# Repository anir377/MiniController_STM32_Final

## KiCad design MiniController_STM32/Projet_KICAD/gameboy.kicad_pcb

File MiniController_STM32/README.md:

# Mini-console STM32 — Projet PCB

Projet réalisé en binôme dans le cadre de la 5e année à **Polytech Nice Sophia**, en spécialité systèmes embarqués.

## Présentation du projet

Notre objectif est de concevoir une carte électronique pour une mini-console de jeu portable. Elle doit réunir un écran TFT, des commandes de jeu, un lecteur microSD, une sortie audio et un moteur vibrant pour le retour haptique. Le travail porte actuellement sur la conception du schéma électronique sous KiCad, le choix des composants et la préparation du futur PCB.

Le microcontrôleur retenu est le **STM32F405RGT6** (ARM Cortex-M4, 168 MHz, 1 Mo de Flash et 192 Ko de RAM), monté directement sur notre carte.

## Composants et blocs électroniques

L'alimentation est prévue à partir d'un **connecteur USB-C**, avec des composants de protection et un convertisseur abaisseur **TLV62569DBV** pour obtenir les 3,3 V nécessaires au système. Les condensateurs de découplage du STM32 ont également été ajoutés. Une alimentation sur batterie est envisagée, mais son circuit de charge et de gestion reste à concevoir.

Pour l'affichage, nous avons prévu un **écran TFT SPI de 4 pouces (480 × 320 pixels)**. Une interface **microSD**, accessible sur le module écran, utilise une liaison SPI distincte pour le stockage des ressources ou des jeux. Les commandes comprennent un **joystick analogique à deux axes avec bouton intégré** et des boutons supplémentaires, notamment Start et Select.

La partie audio comporte un circuit d'amplification et un connecteur pour haut-parleur ; elle est encore en cours de finalisation. Nous avons aussi ajouté un **moteur vibrant ERM** (LCM1027A2445F), commandé par un MOSFET AO3400A et un signal PWM du STM32, avec diode de protection et composants associés.

Le schéma prévoit par ailleurs un **quartz externe (HSE)**, un connecteur de programmation/débogage de type **JTAG/SWD** et un connecteur UART pour le diagnostic. Ces interfaces doivent encore être vérifiées et raccordées complètement.

## Configuration du STM32

Nous utilisons **STM32CubeMX** pour préparer l'affectation des broches et des périphériques du STM32. Le fichier `MiniConsole_STM32.ioc` contient notamment les configurations de SPI1 pour l'écran, SPI2 pour la microSD, ADC1 pour le joystick et TIM4 pour la commande PWM du moteur vibrant.

Ces choix doivent rester cohérents avec les connexions du schéma KiCad. Le développement et les essais du firmware ne constituent pas encore un livrable terminé.

## Avancement et travail restant

Les principaux blocs de la mini-console sont maintenant représentés dans le schéma. **Le projet est encore en phase de conception et n'est pas prêt à être fabriqué.** Il reste notamment à vérifier l'ensemble des réseaux d'alimentation, terminer les connexions de programmation, du quartz, des boutons et de l'audio, ainsi qu'à valider les caractéristiques et les empreintes des composants.

Les prochaines étapes seront la correction des erreurs ERC, la finalisation des bibliothèques et des références JLCPCB, puis le placement et le routage du **PCB quatre couches**, avant la préparation des fichiers de fabrication et d'assemblage.

## Fichiers du dépôt

- **[Projet KiCad](Projet_KICAD/Projet_PCBPolytech_git.kicad_pro)** : projet électronique à ouvrir dans KiCad.
- **[Schéma KiCad](Projet_KICAD/Projet_PCBPolytech_git.kicad_sch)** : schéma électrique en cours de réalisation.
- **[Configuration STM32CubeMX](MiniConsole_STM32.ioc)** : affectation des broches et configuration des périphériques.

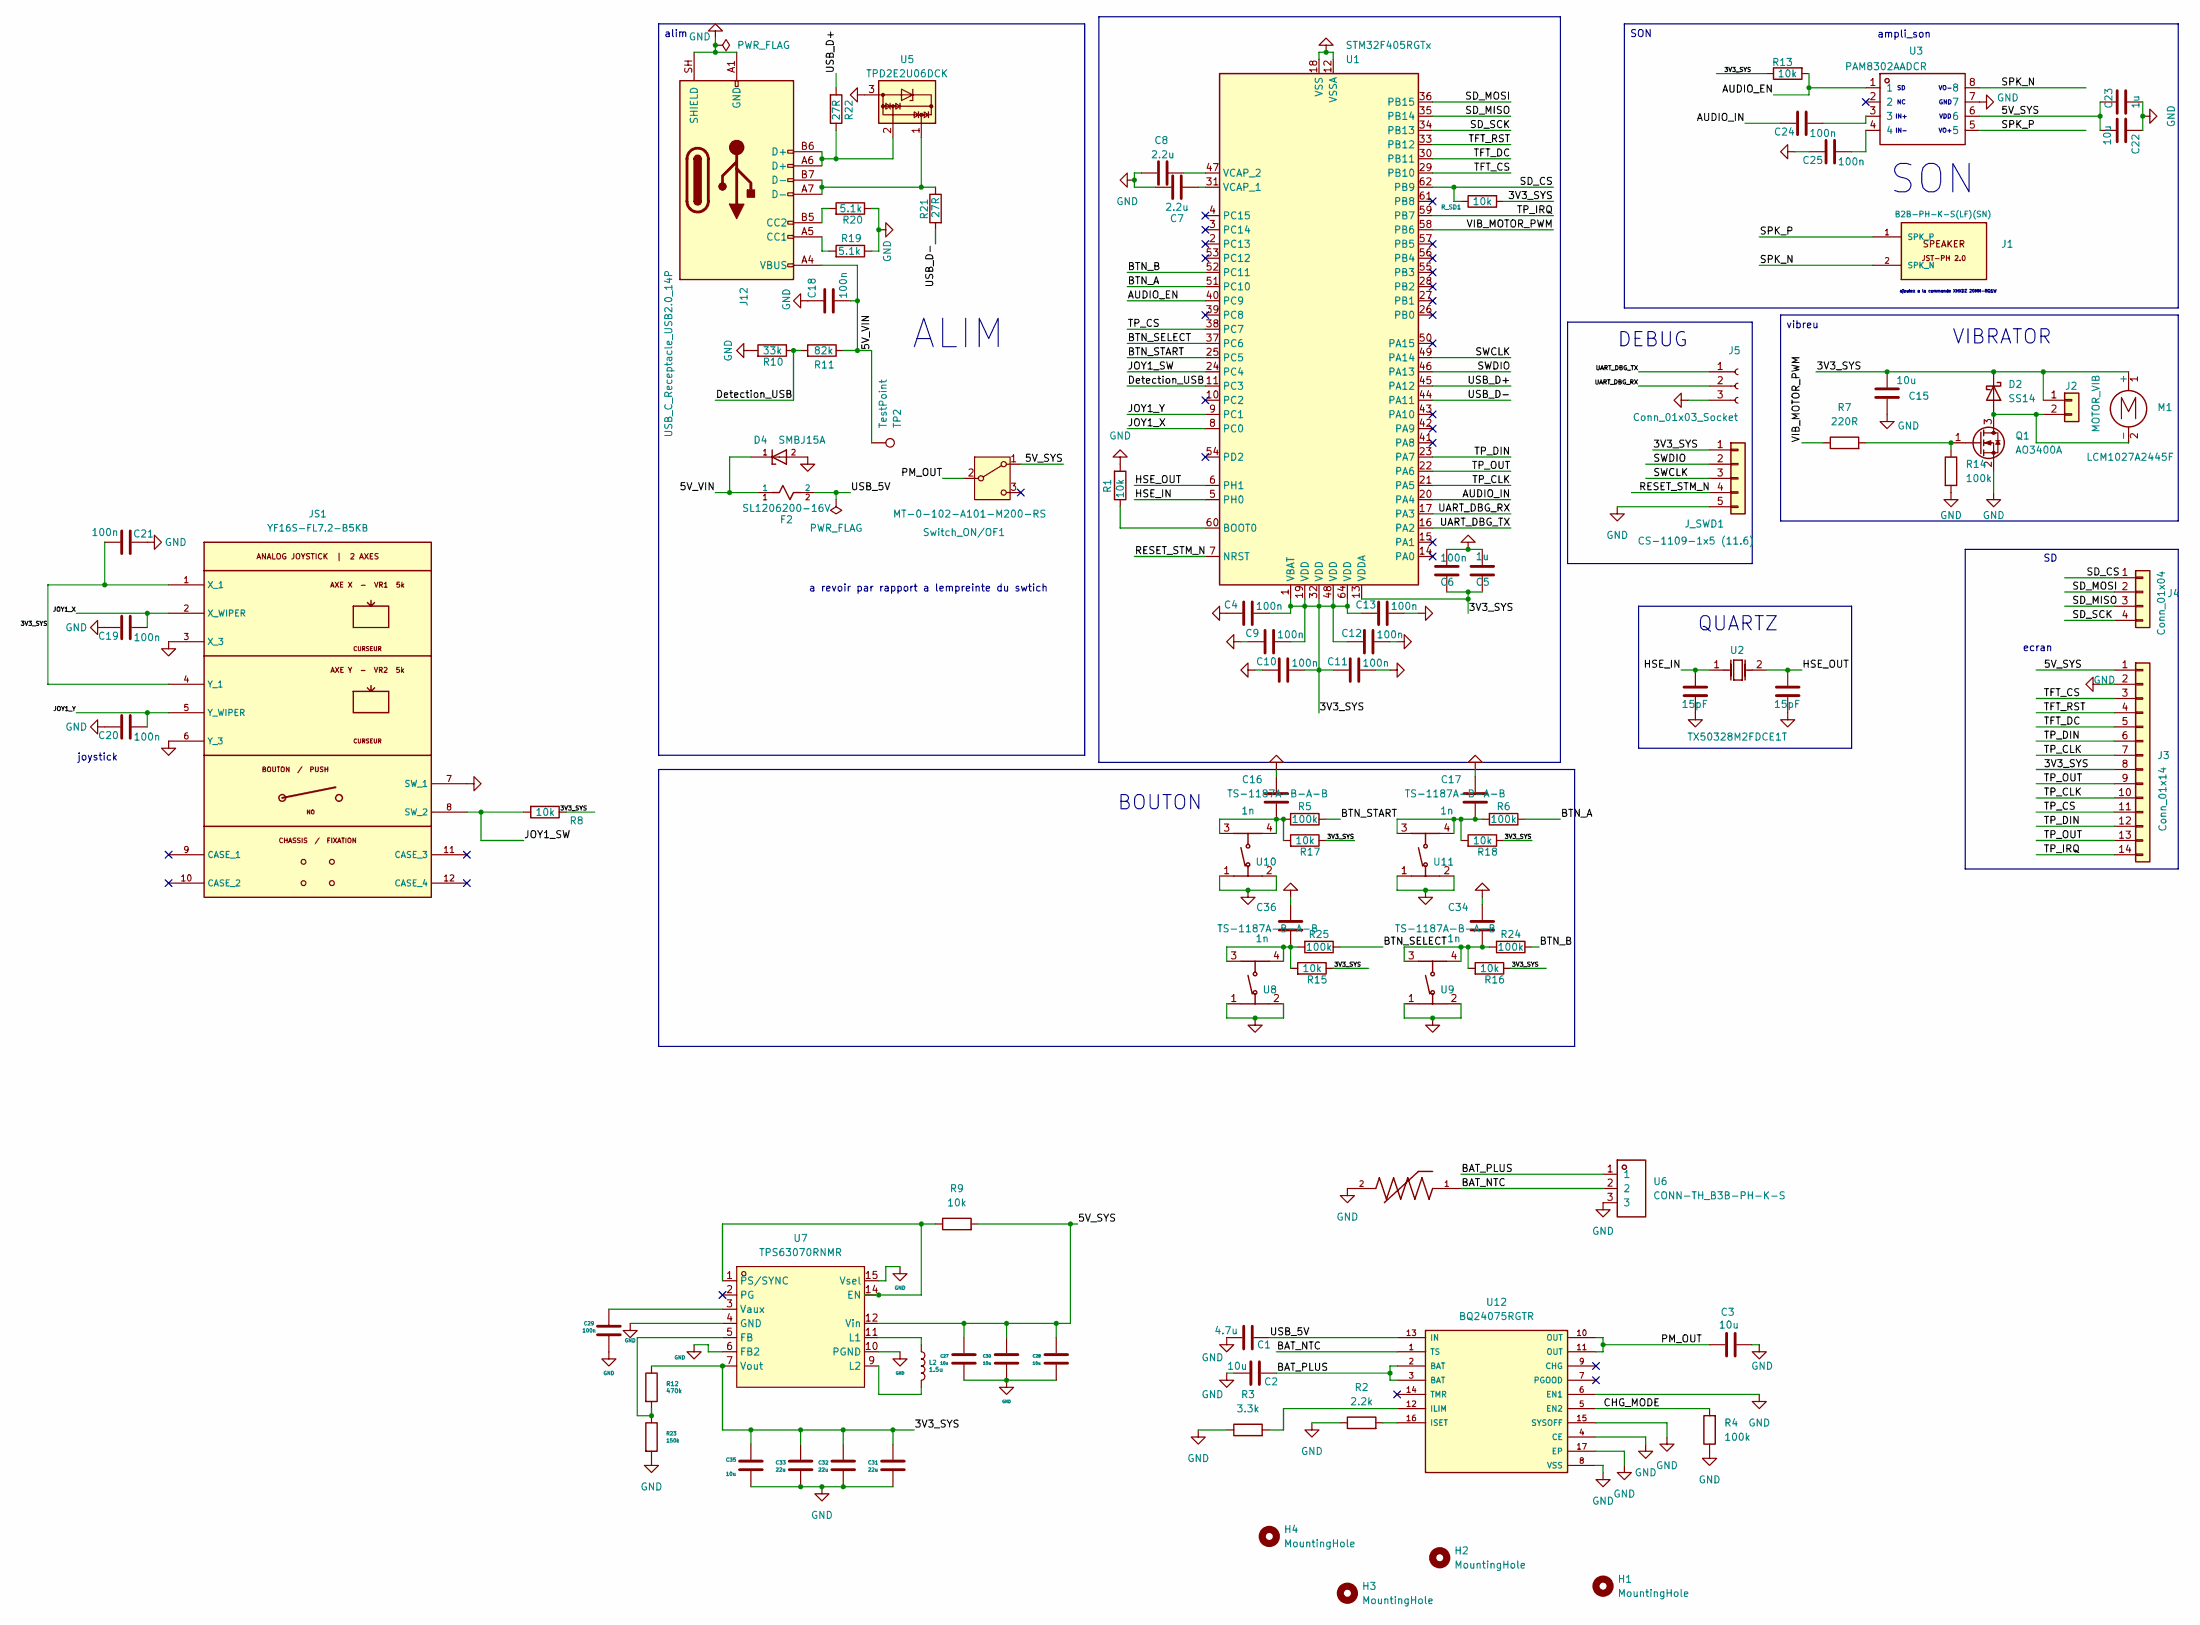
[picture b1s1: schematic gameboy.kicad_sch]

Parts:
C1: 4.7u; C_0805_2012Metric; LCSC C49326719
C2, C3, C15, C22, C27, C28, C30: 10u; C_0805_2012Metric; LCSC C15850
C4, C6, C9, C10, C11, C12, C18, C19, C20, C21, C24, C25, C29: 100n; C_0603_1608Metric; LCSC C14663
C5: 1u; C_0805_2012Metric
C7, C8: 2.2u; C_0805_2012Metric; LCSC C1731
C13: 100n; C_0805_2012Metric; LCSC C14663
C14, C26: 15pF; C_0603_1608Metric
C16, C17, C34, C36: 1n; C_0603_1608Metric; LCSC C131031
C23: 1u; C_0805_2012Metric; LCSC C376925
C31, C32, C33: 22u; C_1206_3216Metric; LCSC C12891
C35: 10u; C_0805_2012Metric
D2: SS14; D_SMA; LCSC C2480
D4: SMBJ15A; D_SMB; PARTREV F2102; LCSC C357961
F2: SL1206200-16V; Fuse_1206_3216Metric; LCSC C50766782
H1, H2, H3, H4: MountingHole; MountingHole_2.2mm_M2
J1: B2B-PH-K-S(LF)(SN); JST_PH_B2B-PH-K_1x02_P2.00mm_Vertical; LCSC Part C131337
J2: MOTOR_VIB; SolderWire-0.1sqmm_1x02_P3.6mm_D0.4mm_OD1mm_Relief
J3: Conn_01x14; PinSocket_1x14_P2.54mm_Vertical; LCSC C2905420
J4: Conn_01x04; PinSocket_1x04_P2.54mm_Vertical; LCSC C2897367
J5: Conn_01x03_Socket; PinHeader_1x03_P2.54mm_Vertical; LCSC C49257
J12: USB_C_Receptacle_USB2.0_14P; USB_C_Receptacle_GCT_USB4085; LCSC C7095263
JS1: YF16S-FL7.2-B5KB; JOYTICK-TH_YF16S-FL7_2-B5KB-45-10-Y_1_YF16S-FL7_2-B5KB_45-1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; MPN YF16S-FL7.2-B5Kb(45-10)-Y; LCSC Part C37323740
J_SWD1: CS-1109-1x5 (11.6); PinHeader_1x05_P2.54mm_Vertical; LCSC C5156614
L2: 1.5u; L_Coilcraft_XxL4020; LCSC Part # C3033018
M1: LCM1027A2445F; LCSC C2759984
Q1: AO3400A; SOT-23; LCSC C20917
R1: 10k; R_0603_1608Metric; LCSC C25804
R2: 2.2k; R_0603_1608Metric; LCSC C4190
R3: 3.3k; R_0603_1608Metric
R4, R5, R6, R14, R24, R25: 100k; R_0603_1608Metric; LCSC C25803
R7: 220R; R_0603_1608Metric; LCSC C22962
R8, R9, R13, R15, R16, R17, R18: 10k; R_0805_2012Metric; LCSC C17414
R10: 33k; R_0603_1608Metric; LCSC C4216
R11: 82k; R_0603_1608Metric; LCSC C23254
R12: 470k; R_0603_1608Metric; LCSC C23178
R19, R20: 5.1k; R_0805_2012Metric; LCSC C2912598
R21, R22: 27R; R_0805_2012Metric; LCSC C2889467
R23: 150k; R_0603_1608Metric; LCSC C22807
RT1: NCP18XH103F03RB; R_0603_1608Metric; LCSC C13564
R_SD1: 10k; R_0603_1608Metric; LCSC C25804
Switch_ON/OF1: MT-0-102-A101-M200-RS; SW-SMD_4P-L5.1-W5.1-P3.70-LS6.5-TL_H1.5; LCSC C1788492
TP2: TestPoint; TestPoint_Pad_D2.0mm
U1: STM32F405RGTx; LQFP-64_10x10mm_P0.5mm; LCSC Part # C15742
U2: TX50328M2FDCE1T; Crystal_SMD_5032-2Pin_5.0x3.2mm; LCSC C5182763
U3: PAM8302AADCR; MSOP-8_3x3mm_P0.65mm; LCSC C113367
U5: TPD2E2U06DCK; SOT-323_SC-70; LCSC C915089
U6: CONN-TH_B3B-PH-K-S; JST_PH_B3B-PH-K_1x03_P2.00mm_Vertical; LCSC C131339
U7: TPS63070RNMR; VQFN-15_L3.0-W2.5-P0.50-BL; MPN TPS63070RNMR; LCSC Part C109322
U8, U9, U10, U11: TS-1187A-B-A-B; SW-SMD_4P-L5.1-W5.1-P3.70-LS6.5-TL_H1.5; LCSC C318884
U12: BQ24075RGTR; VQFN-16-1EP_3x3mm_P0.5mm_EP1.68x1.68mm; LCSC Part # C15464

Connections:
/3V3_SYS: C4.2, C5.1, C6.1, C9.2, C10.2, C11.1, C12.1, C13.1, C15.2, C21.1, C31.1, C32.1, C33.1, C35.1, D2.1 (K), J2.1, J3.8, JS1.1 (X_1), JS1.4 (Y_1), J_SWD1.1, M1.1 (+), R8.1, R12.1, R13.1, R15.1, R16.1, R17.1, R18.1, R_SD1.2, U1.1 (VBAT), U1.13 (VDDA), U1.19 (VDD), U1.32 (VDD), U1.48 (VDD), U1.64 (VDD), U7.7 (Vout)
/5V_SYS: C22.2, C23.1, C27.1, C28.1, C30.1, J3.1, R9.2, Switch_ON/OF1.1 (A), U3.6, U7.12 (Vin)
/5V_VIN: C18.2, D4.1, F2.1, J12.A4 (VBUS), J12.A9 (VBUS), J12.B4 (VBUS), J12.B9 (VBUS), R11.1, TP2.1 (1_1)
/AUDIO_EN: R13.2, U1.40 (PC9), U3.1
/AUDIO_IN: C24.2, U1.20 (PA4)
/BAT_NTC: RT1.1, U6.2, U12.1 (TS)
/BAT_PLUS: C2.1, U6.1, U12.2 (BAT), U12.3 (BAT)
/BTN_A: R6.1, U1.51 (PC10)
/BTN_B: R24.1, U1.52 (PC11)
/BTN_SELECT: R25.1, U1.37 (PC6)
/BTN_START: R5.1, U1.25 (PC5)
/CHG_MODE: R4.2, U12.5 (EN2)
/Detection_USB: R10.1, R11.2, U1.11 (PC3)
/HSE_IN: C14.2, U1.5 (PH0), U2.1
/HSE_OUT: C26.2, U1.6 (PH1), U2.2
/JOY1_SW: JS1.8 (SW_2), R8.2, U1.24 (PC4)
/JOY1_X: C19.1, JS1.2 (X_WIPER), U1.8 (PC0)
/JOY1_Y: C20.1, JS1.5 (Y_WIPER), U1.9 (PC1)
/PM_OUT: C3.1, Switch_ON/OF1.2 (B), U12.10 (OUT), U12.11 (OUT)
/RESET_STM_N: J_SWD1.4, U1.7 (NRST)
/SD_CS: J4.1, R_SD1.1, U1.62 (PB9)
/SD_MISO: J4.3, U1.35 (PB14)
/SD_MOSI: J4.2, U1.36 (PB15)
/SD_SCK: J4.4, U1.34 (PB13)
/SPK_N: J1.2 (SPK_N), U3.8
/SPK_P: J1.1 (SPK_P), U3.5
/SWCLK: J_SWD1.3, U1.49 (PA14)
/SWDIO: J_SWD1.2, U1.46 (PA13)
/TFT_CS: J3.3, U1.29 (PB10)
/TFT_DC: J3.5, U1.30 (PB11)
/TFT_RST: J3.4, U1.33 (PB12)
/TP_CLK: J3.7, J3.10, U1.21 (PA5)
/TP_CS: J3.11, U1.38 (PC7)
/TP_DIN: J3.6, J3.12, U1.23 (PA7)
/TP_IRQ: J3.14, U1.59 (PB7)
/TP_OUT: J3.9, J3.13, U1.22 (PA6)
/UART_DBG_RX: J5.2, U1.17 (PA3)
/UART_DBG_TX: J5.1, U1.16 (PA2)
/USB_5V: C1.1, F2.2, U12.13 (IN)
/USB_D+: R22.2, U1.45 (PA12)
/USB_D-: R21.2, U1.44 (PA11)
/VIB_MOTOR_PWM: R7.1, U1.58 (PB6)
GND: C1.2, C2.2, C3.2, C4.1, C5.2, C6.2, C7.1, C8.1, C9.1, C10.1, C11.2, C12.2, C13.2, C14.1, C15.1, C16.1, C17.1, C18.1, C19.2, C20.2, C21.2, C22.1, C23.2, C25.2, C26.1, C27.2, C28.2, C29.2, C30.2, C31.2, C32.2, C33.2, C34.1, C35.2, C36.1, D4.2, J3.2, J5.3, J12.A1 (GND), J12.A12 (GND), J12.B1 (GND), J12.B12 (GND), J12.SH (SHIELD), JS1.3 (X_3), JS1.6 (Y_3), JS1.7 (SW_1), J_SWD1.5, Q1.2 (S), R1.2, R2.1, R3.1, R4.1, R10.2, R14.2, R19.1, R20.1, R23.2, RT1.2, U1.12 (VSSA), U1.18 (VSS), U1.63 (VSS), U3.7, U5.3, U6.3, U7.4 (GND), U7.6 (FB2), U7.10 (PGND), U7.15 (Vsel), U8.1, U8.2, U9.1, U9.2, U10.1, U10.2, U11.1, U11.2, U12.4 (CE), U12.6 (EN1), U12.8 (VSS), U12.15 (SYSOFF), U12.17 (EP)
unnamed: C16.2, R5.2, R17.2, U10.3, U10.4
unnamed: C17.2, R6.2, R18.2, U11.3, U11.4
unnamed: C24.1, U3.3
unnamed: C25.1, U3.4
unnamed: C34.2, R16.2, R24.2, U9.3, U9.4
unnamed: C36.2, R15.2, R25.2, U8.3, U8.4
unnamed: D2.2 (A), J2.2, M1.2 (-), Q1.3 (D)
unnamed: J12.A5 (CC1), R19.2
unnamed: J12.B5 (CC2), R20.2
unnamed: J12.A6 (D+), J12.B6 (D+), R22.1, U5.2
unnamed: J12.A7 (D-), J12.B7 (D-), R21.1, U5.1
unnamed: Q1.1 (G), R7.2, R14.1
unnamed: R1.1, U1.60 (BOOT0)
unnamed: C7.2, U1.31 (VCAP_1)
unnamed: C8.2, U1.47 (VCAP_2)
unnamed: R9.1, U7.1 (PS/SYNC), U7.14 (EN)
unnamed: R12.2, R23.1, U7.5 (FB)
unnamed: L2.1, U7.11 (L1)
unnamed: L2.2, U7.9 (L2)
unnamed: C29.1, U7.3 (Vaux)
unnamed: R3.2, U12.12 (ILIM)
unnamed: R2.2, U12.16 (ISET)

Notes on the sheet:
ampli_son
IN-
QUARTZ
ecran
VO+
VDD
VO-
SON
a revoir par rapport a lempreinte du swtich
GND
IN+
joystick
DEBUG
ALIM
BOUTON
VIBRATOR
ajoutez a la commande XHXDZ 20MM-8Ω1W
vibreu
alim

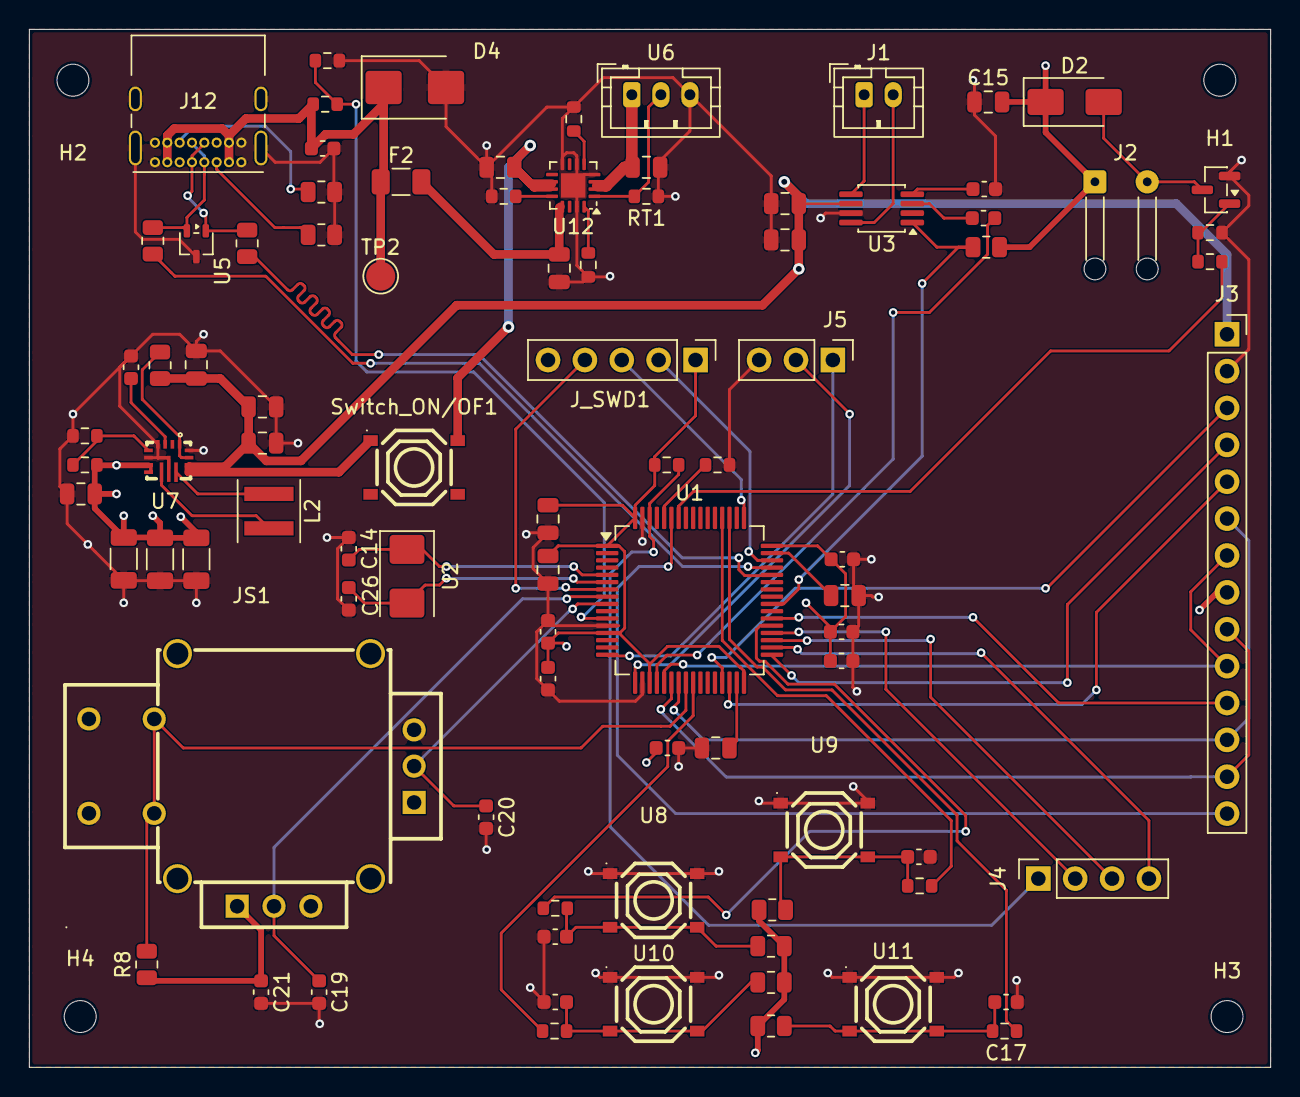
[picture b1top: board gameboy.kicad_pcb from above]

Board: 4 copper layers, 85.5 x 71.5 mm, 93 parts (0 on the bottom side), 65 nets.

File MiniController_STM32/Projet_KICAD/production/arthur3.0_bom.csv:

Designator,Footprint,Quantity,Value,LCSC Part #
C1,0805,1,4.7u,C49326719
"C10, C11, C12, C18, C19, C20, C21, C24, C25, C29, C4, C6, C9",0603,13,100n,C14663
C13,0805,1,100n,C14663
"C14, C26",0603,2,15pF,
"C15, C2, C22, C27, C28, C3, C30",0805,7,10u,C15850
"C16, C17, C34, C36",0603,4,1n,C131031
C23,0805,1,1u,C376925
"C31, C32, C33",1206,3,22u, C12891
C35,0805,1,10u,
C5,0805,1,1u,
"C7, C8",0805,2,2.2u,C1731
D2,D_SMA,1,SS14,C2480
D4,D_SMB,1,SMBJ15A,C357961
F2,1206,1,SL1206200-16V,C50766782
J1,JST_PH_B2B-PH-K_1x02_P2.00mm_Vertical,1,B2B-PH-K-S(LF)(SN),C131337
J12,USB_C_Receptacle_GCT_USB4085,1,USB_C_Receptacle_USB2.0_14P,C7095263
J2,SolderWire-0.1sqmm_1x02_P3.6mm_D0.4mm_OD1mm_Relief,1,MOTOR_VIB,
J3,PinSocket_1x14_P2.54mm_Vertical,1,Conn_01x14,C2905420
J4,PinSocket_1x04_P2.54mm_Vertical,1,Conn_01x04,C2897367
J5,PinHeader_1x03_P2.54mm_Vertical,1,Conn_01x03_Socket,C49257
JS1,JOYTICK-TH_YF16S-FL7_2-B5KB-45-10-Y_1_YF16S-FL7_2-B5KB_45-10_-Y_C37323740,1,YF16S-FL7.2-B5KB,C37323740
J_SWD1,PinHeader_1x05_P2.54mm_Vertical,1,CS-1109-1x5 (11.6),C5156614
L2,L_Coilcraft_XxL4020,1,1.5u,C3033018
Q1,SOT-23,1,AO3400A,C20917
R1,0603,1,10k,C25804
R10,0603,1,33k,C4216
R11,0603,1,82k,C23254
R12,0603,1,470k,C23178
"R13, R15, R16, R17, R18, R8, R9",0805,7,10k,C17414
R14,0603,1,100k,C25803
"R19, R20",0805,2,5.1k,C2912598
R2,0603,1,2.2k, C4190
R21,0805,1,27R,C2889467
R22,0805,1,27R,C2889467 
R23,0603,1,150k,C22807
"R24, R25, R4, R5, R6",0603,5,100k, C25803
R3,0603,1,3.3k,
R7,0603,1,220R,C22962
RT1,0603,1,NCP18XH103F03RB,C13564
R_SD1,0603,1,10k, C25804
SWITCH_ON/OF1,SW-SMD_4P-L5.1-W5.1-P3.70-LS6.5-TL_H1.5,1,MT-0-102-A101-M200-RS,C318884
TP2,TestPoint_Pad_D2.0mm,1,TestPoint,
U1,LQFP-64_10x10mm_P0.5mm,1,STM32F405RGTx,C15742
"U10, U11, U8, U9",SW-SMD_4P-L5.1-W5.1-P3.70-LS6.5-TL_H1.5,4,TS-1187A-B-A-B,C318884
U12,VQFN-16-1EP_3x3mm_P0.5mm_EP1.68x1.68mm,1,BQ24075RGTR,C15464
U2,Crystal_SMD_5032-2Pin_5.0x3.2mm,1,TX50328M2FDCE1T,C5182763
U3,MSOP-8_3x3mm_P0.65mm,1,PAM8302AADCR,C113367
U5,SOT-323_SC-70,1,TPD2E2U06DCK,C915089
U6,JST_PH_B3B-PH-K_1x03_P2.00mm_Vertical,1,CONN-TH_B3B-PH-K-S, C131339
U7,VQFN-15_L3.0-W2.5-P0.50-BL,1,TPS63070RNMR,C109322

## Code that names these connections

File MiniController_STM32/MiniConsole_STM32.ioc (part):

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Mcu.Name=STM32F405RGTx
Mcu.Package=LQFP64
Mcu.UserName=STM32F405RGTx
PA13.Mode=Serial_Wire
PA13.Signal=SYS_JTMS-SWDIO
PA14.Mode=Serial_Wire
PA14.Signal=SYS_JTCK-SWCLK
PA2.Mode=Asynchronous
PA2.Signal=USART2_TX
PA3.Mode=Asynchronous
PA3.Signal=USART2_RX
PA5.Mode=Full_Duplex_Master
PA5.Signal=SPI1_SCK
PA6.Mode=Full_Duplex_Master
PA6.Signal=SPI1_MISO
PA7.Mode=Full_Duplex_Master
PA7.Signal=SPI1_MOSI
PB10.Signal=GPIO_Output
PB11.Signal=GPIO_Output
PB12.Signal=GPIO_Output
PB13.Mode=Full_Duplex_Master
PB13.Signal=SPI2_SCK
PB14.Mode=Full_Duplex_Master
PB14.Signal=SPI2_MISO
PB15.Mode=Full_Duplex_Master
PB15.Signal=SPI2_MOSI
PB6.GPIOParameters=GPIO_Label
PB6.GPIO_Label=VIB_MOTOR_PWM
PB6.Signal=S_TIM4_CH1
PB7.GPIOParameters=GPIO_PuPd,GPIO_Label
PB7.GPIO_Label=TP_IRQ
PB7.GPIO_PuPd=GPIO_PULLUP
PB7.Signal=GPIO_Input
PB9.GPIOParameters=PinState,GPIO_Label
PB9.GPIO_Label=SD_CS
PB9.PinState=GPIO_PIN_SET
PB9.Signal=GPIO_Output
PC0.Signal=ADCx_IN10
PC1.Signal=ADCx_IN11
PC4.GPIOParameters=GPIO_PuPd,GPIO_Label
PC4.GPIO_Label=JOY1_SW
PC4.GPIO_PuPd=GPIO_PULLUP
PC4.Signal=GPIO_Input
PC5.GPIOParameters=GPIO_Label
PC5.GPIO_Label=BTN_START
PC5.Signal=GPIO_Input
PC6.GPIOParameters=GPIO_Label
PC6.GPIO_Label=BTN_SELECT
PC6.Signal=GPIO_Input
PC7.GPIOParameters=GPIO_Label
PC7.GPIO_Label=TP_CS
PC7.Signal=GPIO_Output
PH0-OSC_IN.Mode=HSE-External-Oscillator
PH0-OSC_IN.Signal=RCC_OSC_IN
PH1-OSC_OUT.Mode=HSE-External-Oscillator
PH1-OSC_OUT.Signal=RCC_OSC_OUT
RCC.HSE_VALUE=8000000
RCC.SYSCLKFreq_VALUE=16000000
board=custom
